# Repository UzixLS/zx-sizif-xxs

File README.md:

## Sizif-XXS
Smallest FPGA-based ZX Spectrum clone with real Z80.

### Tech specs
* Two PCB varians: 100x24.5mm (main version) and 65x30mm (Zero version) - both are functionally identical, differs only in size
* PS/2 keyboard
* Pentagon, Spectrum 128, Spectrum 48 and Spectrum +3e modes
* Altera EP1C3T100 FPGA
* Real Z80 with 3.5MHz, 4.4MHz, 5.2MHz, 7MHz (no-wait turbo) and 14MHz (turbo with wait-states) modes
* 512K RAM
* TurboSound with switchable stereo ABC/ACB/mono output
* Integrated DivMMC and Z-Controller, 1x microSD socket
* PAL video output (AV cable like in Raspberry Pi)
* ULAplus
* SpecDrum
* Covox (Pentagon standard - port #FD)
* SounDrive (4-channel stereo covox - ports #0F, #1F, #4F, #5F)
* Tape input via 3.5" jack
* USB 5V power supply

### Magic button
Sizif has a number of configurable parameters that you can change on the fly. To do this just hold Magic button for a second.

To navigate menu you can use up-down keys, to change value use enter or left-right keys. Kempston, Sinclair, Cursor and QAOP supported.

If you press Magic button for a short time, the standard NMI handler 'll be called.

### PS/2 keyboard buttons
| Button | Function |
| - | - |
| F1 | Pause |
| F5 | Magic button |
| F10 | Reboot |
| F12 | Reboot |
| Ctrl+Alt+Del | Reboot |
| Ctrl+Alt+Backspace | Reboot |
| Numpad 8, 2/5, 4, 6 | Joystick's up-down-left-right |
| Numpad 0/Enter | Joystick's fire |
| Alt | Joystick's fire |

### RAM
Sizif contains 512K RAM. 128K available via 7FFDh port, 128K via DFFDh (Profi standart, most compatible with old 128K software) and 128K used for DivMMC. Remaining space used to store ROM. Note that DFFDh port available only in Pentagon mode.

### SD card
Sizif have preinstalled esxDOS firmware, which provides ability to load TAP, TRD, SCL, Z80 files and save snapshots. To use this you should format SD cart to FAT32 or FAT16 and unpack latest esxDOS release ([link](http://www.esxdos.org/index.html)) to card. Also it's recommended to install Long Filename Browser ([link](https://spectrumcomputing.co.uk/forums/viewtopic.php?t=2553)) to card.

### How to program
There is two options:
1. Program via JTAG connector using USB blaster and Quartus Programmer - use jic file from out folder.
2. Program flash chip directly using TL866 or similar device - use bin file.

### Changelog & current status
* Rev.A - first release. Please note the [errata](pcb/rev.A/ERRATA.txt).
* Rev.B:
    * fixed all rev.A issues
    * fixed "jailbars" on video output
    * 0805 footprints replaced with 0603
    * tape input moved slightly away to not to interfere with wide AV jack
    * 3.5 jacks replaced with THT variant for better reliability
    * changed ps/2 header orientation
* Zero Rev.A - first release of Zero version. Based on Rev.B of main pcb.

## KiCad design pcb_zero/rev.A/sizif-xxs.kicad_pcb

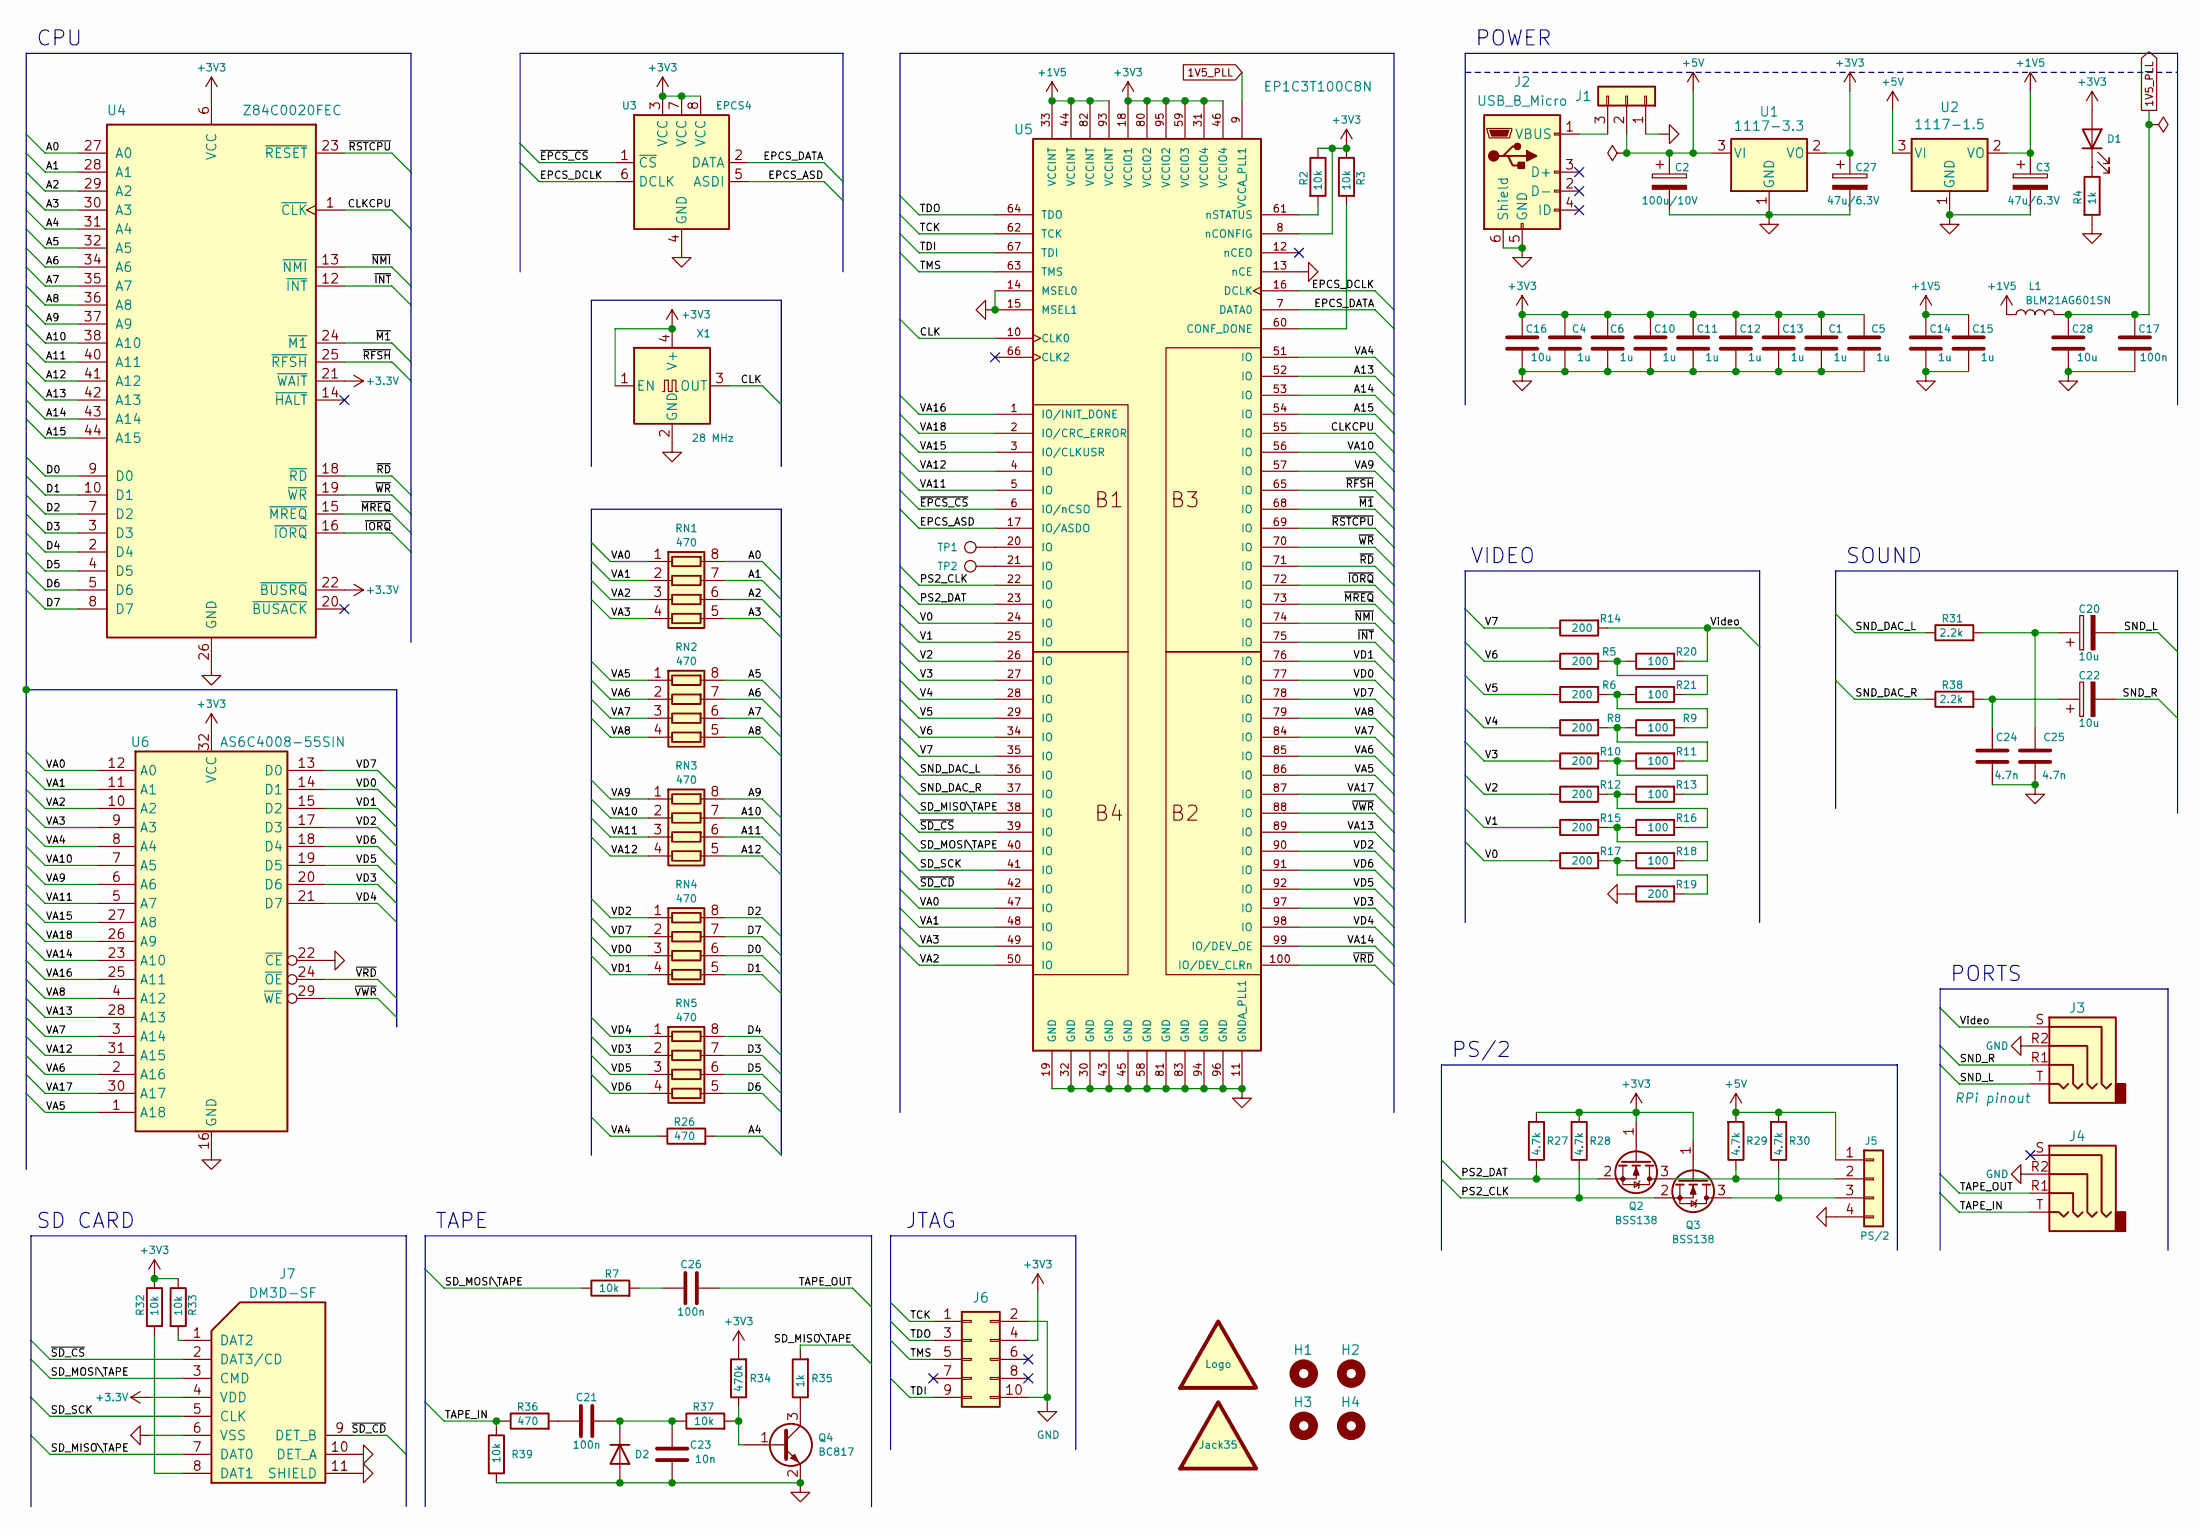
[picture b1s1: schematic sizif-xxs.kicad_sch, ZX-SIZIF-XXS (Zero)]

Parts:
C1, C4, C5, C6, C10, C11, C12, C13, C14, C15: 1u; C_0603_1608Metric_Pad1.08x0.95mm_HandSolder
C2: 100u/10V; CP_EIA-7343-31_Kemet-D_Pad2.25x2.55mm_HandSolder
C3, C27: 47u/6.3V; CP_EIA-3528-21_Kemet-B_Pad1.50x2.35mm_HandSolder
C16, C28: 10u; C_0805_2012Metric_Pad1.18x1.45mm_HandSolder
C17, C21, C26: 100n; C_0603_1608Metric_Pad1.08x0.95mm_HandSolder
C20, C22: 10u; CP_EIA-3216-18_Kemet-A_Pad1.58x1.35mm_HandSolder
C23: 10n; C_0603_1608Metric_Pad1.08x0.95mm_HandSolder
C24, C25: 4.7n; C_0603_1608Metric_Pad1.08x0.95mm_HandSolder
D1: LED; LED_1210_3225Metric_Pad1.42x2.65mm_HandSolder
D2: 1N4148W; D_SOD-123
H1, H2, H3, H4: MountingHole; MountingHole_2.7mm_M2.5
J1: Pin header 1x3 Pitch=2.54mm; PinHeader_1x03_P2.54mm_Vertical
J2: USB_B_Micro; USB_Micro-B_Molex-105017-0001
J3, J4: PJ-320; Jack_3.5mm_PJ320D_Horizontal
J5: Pin header 1x4 Pitch=2.54mm; PinHeader_1x04_P2.54mm_Vertical
J6: Pin header 2x5 Pitch=2.54mm; PinHeader_2x05_P2.54mm_Vertical
J7: DM3D-SF; microSD_HC_Hirose_DM3D-SF
L1: BLM21AG601SN; L_0805_2012Metric_Pad1.15x1.40mm_HandSolder
LOGO1: graphic; black-mage-9.6x6.5
LOGO2: Jack35; jack35_4pin
Q2, Q3: BSS138; SOT-23
Q4: BC817; SOT-23
R2, R3, R7, R32, R33, R37, R39: 10k; R_0603_1608Metric_Pad0.98x0.95mm_HandSolder
R4, R35: 1k; R_0603_1608Metric_Pad0.98x0.95mm_HandSolder
R5, R6, R8, R10, R12, R14, R15, R17, R19: 200; R_0603_1608Metric_Pad0.98x0.95mm_HandSolder
R9, R11, R13, R16, R18, R20, R21: 100; R_0603_1608Metric_Pad0.98x0.95mm_HandSolder
R26, R36: 470; R_0603_1608Metric_Pad0.98x0.95mm_HandSolder
R27, R28, R29, R30: 4.7k; R_0603_1608Metric_Pad0.98x0.95mm_HandSolder
R31, R38: 2.2k; R_0603_1608Metric_Pad0.98x0.95mm_HandSolder
R34: 470k; R_0603_1608Metric_Pad0.98x0.95mm_HandSolder
RN1, RN2, RN3, RN4, RN5: 470; R_Array_Convex_4x0603
TP1, TP2: TestPoint; TestPoint_Pad_D1.0mm
U1: 1117-3.3; SOT-223-3_TabPin2
U2: 1117-1.5; SOT-223-3_TabPin2
U3: EPCS4; SOIC-8_3.9x4.9mm_P1.27mm
U4: Z84C0020FEC; TQFP-44_14x14mm_P0.8mm
U5: EP1C3T100C8N; TQFP-100_14x14mm_P0.5mm
U6: AS6C4008-55SIN; SSOP-32_11.305x20.495mm_P1.27mm
X1: 28 MHz; Oscillator_SMD_SeikoEpson_SG8002CA-4Pin_7.0x5.0mm

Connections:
1V5_PLL: C17.2, C28.2, L1.2, U5.9 (VCCA_PLL1)
+1V5: C3.1, C14.1, C15.2, L1.1, U2.2 (VO), U5.33 (VCCINT), U5.44 (VCCINT), U5.82 (VCCINT), U5.93 (VCCINT)
+5V: C2.1, J1.2, J5.1, R29.2, R30.2, U1.3 (VI), U2.3 (VI)
/A0: RN1.8 (R1.2), U4.27 (A0)
/A1: RN1.7 (R2.2), U4.28 (A1)
/A2: RN1.6 (R3.2), U4.29 (A2)
/A3: RN1.5 (R4.2), U4.30 (A3)
/A4: R26.2, U4.31 (A4)
/A5: RN2.8 (R1.2), U4.32 (A5)
/A6: RN2.7 (R2.2), U4.34 (A6)
/A7: RN2.6 (R3.2), U4.35 (A7)
/A8: RN2.5 (R4.2), U4.36 (A8)
/A9: RN3.8 (R1.2), U4.37 (A9)
/A10: RN3.7 (R2.2), U4.38 (A10)
/A11: RN3.6 (R3.2), U4.40 (A11)
/A12: RN3.5 (R4.2), U4.41 (A12)
/A13: U4.42 (A13), U5.52 (IO)
/A14: U4.43 (A14), U5.53 (IO)
/A15: U4.44 (A15), U5.54 (IO)
/CLK: U5.10 (CLK0), X1.3 (OUT)
/CLKCPU: U4.1 (~CLK), U5.55 (IO)
/D0: RN4.6 (R3.2), U4.9 (D0)
/D1: RN4.5 (R4.2), U4.10 (D1)
/D2: RN4.8 (R1.2), U4.7 (D2)
/D3: RN5.7 (R2.2), U4.3 (D3)
/D4: RN5.8 (R1.2), U4.2 (D4)
/D5: RN5.6 (R3.2), U4.4 (D5)
/D6: RN5.5 (R4.2), U4.5 (D6)
/D7: RN4.7 (R2.2), U4.8 (D7)
/EPCS_ASD: U3.5 (ASDI), U5.17 (IO/ASDO)
/EPCS_DATA: U3.2 (DATA), U5.7 (DATA0)
/EPCS_DCLK: U3.6 (DCLK), U5.16 (DCLK)
/PS2_CLK: Q3.2 (S), R28.1, U5.22 (IO)
/PS2_DAT: Q2.2 (S), R27.1, U5.23 (IO)
/SD_MISO\TAPE: J7.7 (DAT0), R35.2, U5.38 (IO)
/SD_MOSI\TAPE: J7.3 (CMD), R7.1, U5.40 (IO)
/SD_SCK: J7.5 (CLK), U5.41 (IO)
/SND_DAC_L: R31.1, U5.36 (IO)
/SND_DAC_R: R38.1, U5.37 (IO)
/SND_L: C20.2, J3.T
/SND_R: C22.2, J3.R1
/TAPE_IN: J4.T, R36.1, R39.1
/TAPE_OUT: C26.1, J4.R1
/TCK: J6.1, U5.62 (TCK)
/TDI: J6.9, U5.67 (TDI)
/TDO: J6.3, U5.64 (TDO)
/TMS: J6.5, U5.63 (TMS)
/V0: R17.1, U5.24 (IO)
/V1: R15.1, U5.25 (IO)
/V2: R12.1, U5.26 (IO)
/V3: R10.1, U5.27 (IO)
/V4: R8.1, U5.28 (IO)
/V5: R6.1, U5.29 (IO)
/V6: R5.1, U5.34 (IO)
/V7: R14.1, U5.35 (IO)
/VA0: RN1.1 (R1.1), U5.47 (IO), U6.12 (A0)
/VA1: RN1.2 (R2.1), U5.48 (IO), U6.11 (A1)
/VA2: RN1.3 (R3.1), U5.50 (IO), U6.10 (A2)
/VA3: RN1.4 (R4.1), U5.49 (IO), U6.9 (A3)
/VA4: R26.1, U5.51 (IO), U6.8 (A4)
/VA5: RN2.1 (R1.1), U5.86 (IO), U6.1 (A18)
/VA6: RN2.2 (R2.1), U5.85 (IO), U6.2 (A16)
/VA7: RN2.3 (R3.1), U5.84 (IO), U6.3 (A14)
/VA8: RN2.4 (R4.1), U5.79 (IO), U6.4 (A12)
/VA9: RN3.1 (R1.1), U5.57 (IO), U6.6 (A6)
/VA10: RN3.2 (R2.1), U5.56 (IO), U6.7 (A5)
/VA11: RN3.3 (R3.1), U5.5 (IO), U6.5 (A7)
/VA12: RN3.4 (R4.1), U5.4 (IO), U6.31 (A15)
/VA13: U5.89 (IO), U6.28 (A13)
/VA14: U5.99 (IO/DEV_OE), U6.23 (A10)
/VA15: U5.3 (IO/CLKUSR), U6.27 (A8)
/VA16: U5.1 (IO/INIT_DONE), U6.25 (A11)
/VA17: U5.87 (IO), U6.30 (A17)
/VA18: U5.2 (IO/CRC_ERROR), U6.26 (A9)
/VD0: RN4.3 (R3.1), U5.77 (IO), U6.14 (D1)
/VD1: RN4.4 (R4.1), U5.76 (IO), U6.15 (D2)
/VD2: RN4.1 (R1.1), U5.90 (IO), U6.17 (D3)
/VD3: RN5.2 (R2.1), U5.97 (IO), U6.20 (D6)
/VD4: RN5.1 (R1.1), U5.98 (IO), U6.21 (D7)
/VD5: RN5.3 (R3.1), U5.92 (IO), U6.19 (D5)
/VD6: RN5.4 (R4.1), U5.91 (IO), U6.18 (D4)
/VD7: RN4.2 (R2.1), U5.78 (IO), U6.13 (D0)
/Video: J3.S, R14.2, R20.2
/~EPCS_CS: U3.1 (~CS), U5.6 (IO/nCSO)
/~INT: U4.12 (~INT), U5.75 (IO)
/~IORQ: U4.16 (~IORQ), U5.72 (IO)
/~M1: U4.24 (~M1), U5.68 (IO)
/~MREQ: U4.15 (~MREQ), U5.73 (IO)
/~NMI: U4.13 (~NMI), U5.74 (IO)
/~RD: U4.18 (~RD), U5.71 (IO)
/~RFSH: U4.25 (~RFSH), U5.65 (IO)
/~RSTCPU: U4.23 (~RESET), U5.69 (IO)
/~SD_CD: J7.9 (DET_B), U5.42 (IO)
/~SD_CS: J7.2 (DAT3/CD), U5.39 (IO)
/~VRD: U5.100 (IO/DEV_CLRn), U6.24 (~OE)
/~VWR: U5.88 (IO), U6.29 (~WE)
/~WR: U4.19 (~WR), U5.70 (IO)
GND: C1.2, C2.2, C3.2, C4.1, C5.2, C6.2, C10.2, C11.2, C12.2, C13.2, C14.2, C15.1, C16.1, C17.1, C23.2, C24.2, C25.2, C27.2, C28.1, D2.2 (A), J1.1, J2.5 (GND), J2.6 (Shield), J3.R2, J4.R2, J5.4, J6.2, J6.10, J7.6 (VSS), J7.10 (DET_A), J7.11 (SHIELD), Q4.2 (E), R4.2, R19.1, R39.2, U1.1 (GND), U2.1 (GND), U3.4 (GND), U4.26 (GND), U5.11 (GNDA_PLL1), U5.13 (nCE), U5.14 (MSEL0), U5.15 (MSEL1), U5.19 (GND), U5.30 (GND), U5.32 (GND), U5.43 (GND), U5.45 (GND), U5.58 (GND), U5.81 (GND), U5.83 (GND), U5.94 (GND), U5.96 (GND), U6.16 (GND), U6.22 (~CE), X1.2 (GND)
unnamed: C20.1, C25.1, R31.2
unnamed: C21.1, C23.1, D2.1 (K), R37.1
unnamed: C21.2, R36.2
unnamed: C22.1, C24.1, R38.2
unnamed: C26.2, R7.2
unnamed: D1.1 (K), R4.1
unnamed: J1.3, J2.1 (VBUS)
unnamed: J5.2, Q2.3 (D), R29.1
unnamed: J5.3, Q3.3 (D), R30.1
unnamed: J7.1 (DAT2), R33.2
unnamed: J7.8 (DAT1), R32.2
unnamed: Q4.1 (B), R34.1, R37.2
unnamed: Q4.3 (C), R35.1
unnamed: R2.2, U5.61 (nSTATUS)
unnamed: R3.2, U5.60 (CONF_DONE)
unnamed: R10.2, R11.1, R13.2
unnamed: R8.2, R9.1, R11.2
unnamed: R12.2, R13.1, R16.2
unnamed: R15.2, R16.1, R18.2
unnamed: R17.2, R18.1, R19.2
unnamed: R5.2, R20.1, R21.2
unnamed: R6.2, R9.2, R21.1
unnamed: TP1.1, U5.20 (IO)
unnamed: TP2.1, U5.21 (IO)

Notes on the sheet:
PS/2
TAPE
PORTS
JTAG
SD CARD
SOUND
POWER
CPU
VIDEO

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
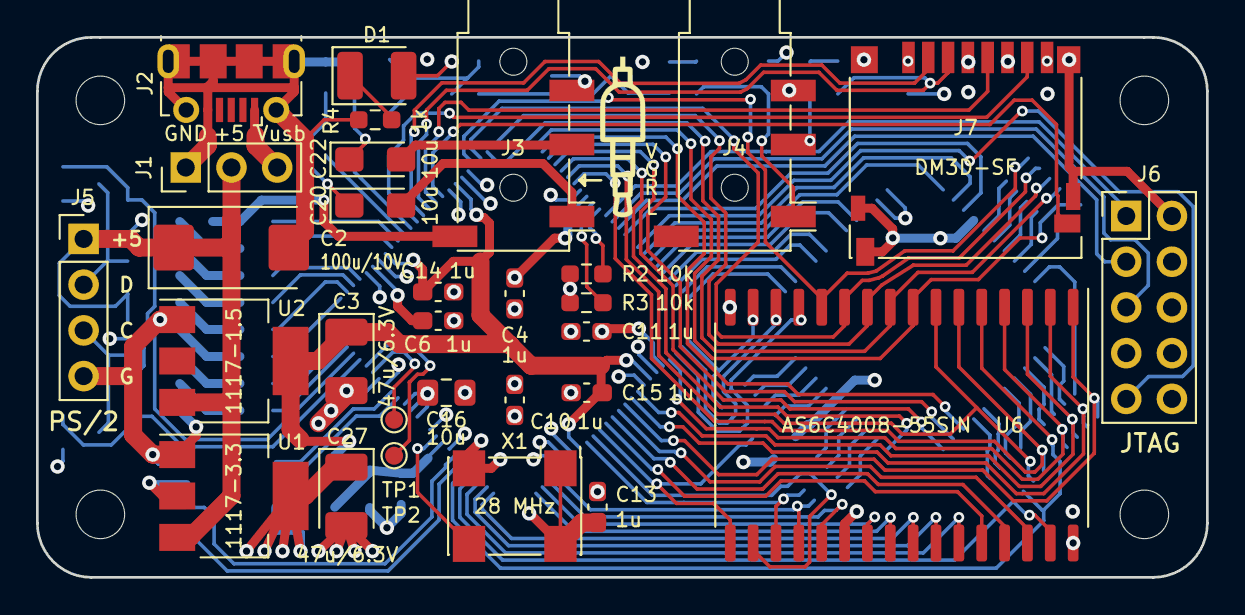
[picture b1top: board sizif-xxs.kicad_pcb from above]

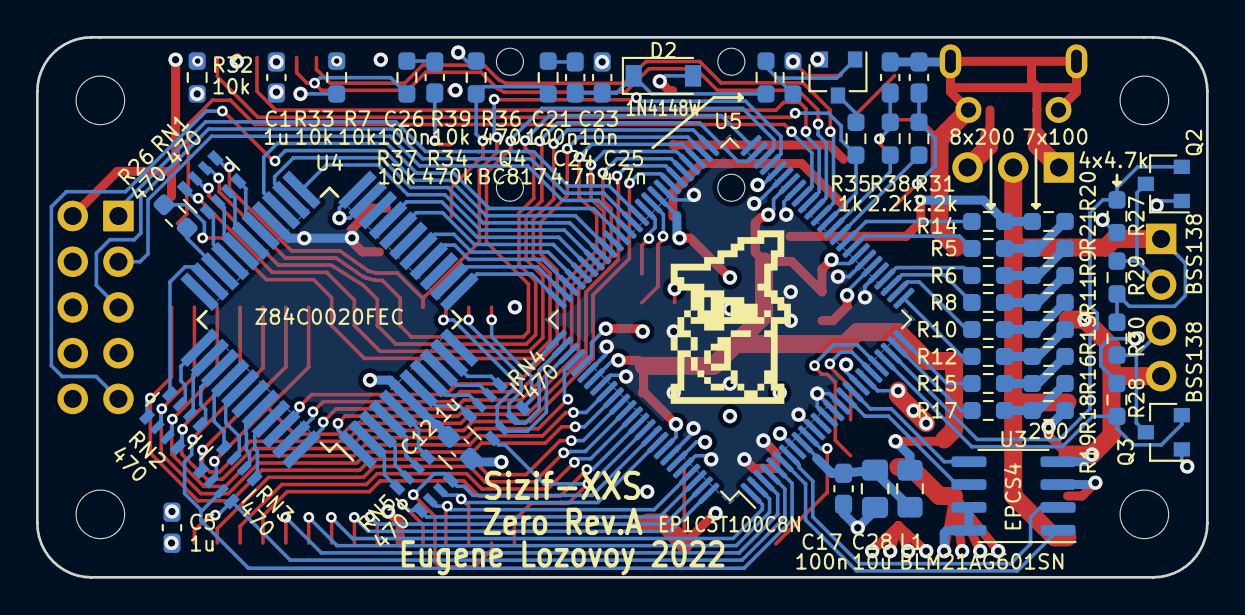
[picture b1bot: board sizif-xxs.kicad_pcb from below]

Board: 4 copper layers, 65.0 x 30.0 mm, 90 parts (55 on the bottom side), 123 nets.

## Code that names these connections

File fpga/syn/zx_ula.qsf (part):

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set_location_assignment PIN_3 -to vd[4]
set_location_assignment PIN_4 -to va[12]
set_location_assignment PIN_5 -to va[11]
set_location_assignment PIN_20 -to ps2_dat
set_location_assignment PIN_21 -to ps2_clk
set_location_assignment PIN_22 -to reserv[0]
set_location_assignment PIN_23 -to reserv[1]
set_location_assignment PIN_24 -to composite[0]
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set_location_assignment PIN_29 -to composite[3]
set_location_assignment PIN_34 -to composite[2]
set_location_assignment PIN_35 -to composite[1]
set_location_assignment PIN_36 -to snd_l
set_location_assignment PIN_37 -to snd_r
set_location_assignment PIN_38 -to sd_cd
set_location_assignment PIN_39 -to sd_cs
set_location_assignment PIN_40 -to sd_miso_tape_in
set_location_assignment PIN_41 -to sd_sck
set_location_assignment PIN_42 -to sd_mosi_tape_out
set_location_assignment PIN_47 -to vd[2]
set_location_assignment PIN_48 -to vd[0]
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set_location_assignment PIN_70 -to va[13]
set_location_assignment PIN_71 -to n_vwr
set_location_assignment PIN_72 -to va[17]
set_location_assignment PIN_73 -to clkcpu
set_location_assignment PIN_74 -to n_wr
set_location_assignment PIN_75 -to n_rd
set_location_assignment PIN_76 -to a[14]
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
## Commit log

2021-05-02 initial
2021-05-02 add pcb rev.A
2021-05-02 initial add fpga sources
2021-05-03 add readme
2021-05-03 fpga: wip
2021-05-04 ps2: add debounce
2021-05-04 ps2: handle more buttons, add kempston
2021-05-04 add turbosound
2021-05-04 fix stability
2021-05-05 ps2: improve kempston layout
2021-05-05 improve boot speed
2021-05-05 fix pal encoding artifacts (temporary)
2021-05-05 soundrive: fix port selecting
2021-05-05 ulaplus fixes
2021-05-05 turbosound fixes
2021-05-05 fix clipping in sound mixer
2021-05-06 ps2: improve handling of simultaneous key presses
2021-05-06 fix garbage when reading nonexisting io ports
2021-05-06 fix switching to turbo 14MHz mode
2021-05-06 add testbench
2021-05-06 minor testbench update
2021-05-06 screen: minor refactor
2021-05-06 significant stability improvements with 48K/128K timings
2021-05-07 disable +3 ports by default to improve compatibility
2021-05-07 add rom files
2021-05-26 add errata for pcb rev.A
2021-05-26 update testbench T80
2021-05-26 refactor testbench makefile
2021-06-14 fpga: remove unused usbhost files
2021-06-14 convert tabs to spaces
2021-06-14 ps2: handle ctrl-alt-backspace as reboot
2021-06-14 some minor refactoring
2021-06-17 fpga: add makefile
2021-06-17 ulaplus.sv: fix indentation
2021-06-17 fpga: fix missing magic sounds
2021-06-17 fpga: prepare for new magic rom
2021-06-17 new magic rom with menu
2021-06-18 mixer: implement panning settings
2021-06-18 magic rom: swap panning abc and acb positions
2021-06-19 magic rom: tune menu position
2021-06-19 magic rom: remove "save & exit" entry; config is now always saved
2021-06-19 draw.asm: slightly reformat screen_map
2021-06-19 divmmc.sv: remove redundant check
2021-06-19 turbosound.sv: add en_ts
2021-06-19 synchronize pause to int and rfsh cycle just for safety
2021-06-19 magic rom: fix ay restore when there is no turbosound
2021-06-19 ps2: don't count alt as fire key when left ctrl is hold
    for ctrl-alt-del
2021-06-19 magic rom: add description strings to rom file
2021-06-20 magic rom: mute saa1099 in menu
2021-06-29 magic: add covox/soundrive and ulaplus configuration
2021-06-30 handle +3 mode with 48K ram
2021-06-30 magic: fix border when entering menu
2021-06-30 magic rom: draw boxes after initing cpld at boot
2021-06-30 magic rom: fix hot switching to +3 mode when basic48 active
2021-06-30 magic rom: fix possible crash on start
2021-07-01 fix palette
2021-07-01 add tape output on sd_mosi pin
2021-09-21 merge latest changes from sizif-512
    * add 4.4 MHz and 5.2 MHz turbo modes
    * handle magic key press if initialization wasn't completed before
    * replace 'timings', 'ram', 'plus3' settings with one 'machine' setting
    * refactor memory controller
    * significantly improve classic timings
    * magic rom: fix 'h' font character
2021-10-26 update pcb rev.A errata
2021-11-14 disable 14mhz mode
    It has been broken for a long time. I don't see any reason to
    investigate my time to fix it as it's doesn't look useful for any
    software.
2021-11-14 fix incorrect pallete after enabling ulaplus in menu
2021-11-14 fix tape out
2021-11-14 mixer: fix abc/acb panning
2021-11-14 mixer: don't switch ABC-ACB panning for second ay in turbosound
    turbosound assume only ABC panning
2021-11-15 replace ym2149 implementation
    new implementation uses less LE's
2021-11-15 replace composite video output implementation
    New one is borrowed from Speccy 2010 project. It's have a much, much
    better output quality in price of increased FPGA resources usage.
2021-11-18 [minor] refactor fpga project
2021-11-18 add Makefile
2021-11-18 testbench: hide useless warnings
2022-01-27 magic rom: fix 'd' font character
2022-01-29 update gitignore
2022-01-29 update Makefile: add new targets (pipeline, pipeline_sof); tiny refactor
2022-02-01 fix io contention
2022-02-01 magic: add ay_en
2022-02-01 fix border size in 128K timings
2022-02-01 fix #1ffd port decoding
2022-02-01 fpga: some minor refactors
2022-02-01 magic rom: refactor
2022-02-01 fix compatibility with some old ps/2 keyboards
2022-02-01 add support for ZC SD card controller; replace NO-OS divmmc mode with ZC
2022-02-01 add 48K rom
2022-02-01 fix ulaplus ghost image on border
2022-02-02 increase colors saturation
2022-02-02 fix unintended snow in 4.4MHz mode
2022-02-19 add license
2022-02-19 add pcb rev.B
2022-02-19 add pcb rev.B gerbers, pdf, etc...
2022-02-19 update photo in readme
2022-03-10 add pcb rev.A pdf and interactive bom
2022-06-26 fix kempston port decoding - add DF port for some rare games
2022-06-26 fix fpga makefile report target
2022-06-26 fix #1ffd +3 port
2022-06-26 make dark colors a bit darker
2022-06-27 fix random garbage on screen
2022-07-01 add pcb zero rev.A
2022-07-01 add pcb zero rev.A gerbers, pdf, etc...
2022-07-01 update jic files
2022-08-15 fix allram mode (broken in d4e706b)
2022-08-20 improve turbo modes reliability
2022-08-20 add specdrum
2022-08-20 fix random garbage on screen (again)
    I hope I've found and fixed root cause of issue in this commit.
2022-10-30 fix ps/2 sticking keys
2022-10-30 change ps/2 keyboard mapping
    * pause has been moved from F12 to F1
    * reboot has been assigned to F10 and F12 (but still present on
    Ctrl-Alt-Del / Ctrl-Alt-Backspace)
2022-10-31 improve compatibility with slower sram chips
2022-11-01 add 14MHz mode
2023-03-24 add fpga firmware file in bin format
2023-10-26 fix support of some ps/2 keyboards with slow clock
2024-01-03 refactor: rename screen->video, memcontrol->mem, cpucontrol->cpu
    no functional changes
2024-01-04 allow nmi call when divmmc's mapram in use
2024-01-05 implement ula+ registers reading
2024-01-06 refactor mixer - optimize fpga resources usage
2024-01-07 rom: minor refactors
2024-01-07 add option to disable sd indication on border
2024-01-07 improve 128 int timings
2024-01-08 refactor memory controller
    Also this commit fixes ula+ io contention for classic timings. This
    affects ham256.tap.
2024-01-10 fix basic 128 crashes when divmmc is enabled
2024-01-10 add auto cpu frequency
    When this feature enabled:
    * Frequency sets to 14MHz on esxdos activity - for fastest loading from
    sd card;
    * Frequency sets to 14MHz on 48 BASIC startup;
    * Frequency sets to 3.5MHz within ~1ms after #FE port access - this
    allows to load from tape within turbo mode. Also this improves beeper
2026-06-17 remove raw=true from README links

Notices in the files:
fpga/syn/zx_ula.qsf:
Copyright (C) 1991-2009 Altera Corporation
